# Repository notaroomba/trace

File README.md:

<h1 align="center">
  <br>
  
  <br>
  Trace
  <br>
</h1>

<h4 align="center">
A comprehensive PCB ruler with essential reference footprints, measurements, and conversions!
</h4>

<div align="center">

</div>

<p align="center">
  <a href="#key-features">Key Features</a> •
  <a href="#pcb">PCB</a> •
  <a href="#credits">Credits</a> •
  <a href="#license">License</a>
</p>

## Key Features

- **310mm x 35mm PCB ruler** with imperial and metric measurements
- **AWG gauge** for wire sizing and via hole measurements
- **Trace thickness reference** for PCB design
- **Protractor** with 5° and 10° angle markings
- **Common component footprints** including:
  - Resistors (various packages)
  - Capacitors (multiple sizes)
  - Inductors
  - Diodes and general components
  - ICs (various packages)
- **MOSFET channel type reference** silkscreen
- **Useful conversions** on the back
- **NFC Tag** to keep owner info / save more conversions/formulas/information

<video width="800" controls poster="assets/trace.jpg">
  <source src="assets/trace_nfc.mp4" type="video/mp4">
  Your browser does not support the video tag. <a href="assets/trace_nfc.mp4">Download the video</a>.
</video>

## PCB

Designed in KiCad as a practical tool for electronics engineers and hobbyists.

### Schematic

### PCB Layout

## Credits

This project uses:

- [KiCad](https://www.kicad.org/)
- [Figma](https://www.figma.com/) for protractor design
- [Hack Club Blueprint](https://blueprint.hackclub.com/)

## You may also like...

- [Cyberboard](https://github.com/NotARoomba/Cyberboard) – A Raspberry Pi Pico-sized STM32 development board with Bluetooth
- [CyberCard](https://github.com/NotARoomba/CyberCard) – A Cyberpunk themed NFC hacker card
- [Niveles De Niveles](https://github.com/NotARoomba/NivelesDeNiveles) – Real-time flood alert app
- [Linea](https://github.com/NotARoomba/Linea) – An EMR tablet
- [Tamaki](https://github.com/NotARoomba/Tamaki) – A cute HackPad

## License

MIT

---

> [notaroomba.dev](https://notaroomba.dev) &nbsp;&middot;&nbsp;
> GitHub [@NotARoomba](https://github.com/NotARoomba) &nbsp;&middot;&nbsp;

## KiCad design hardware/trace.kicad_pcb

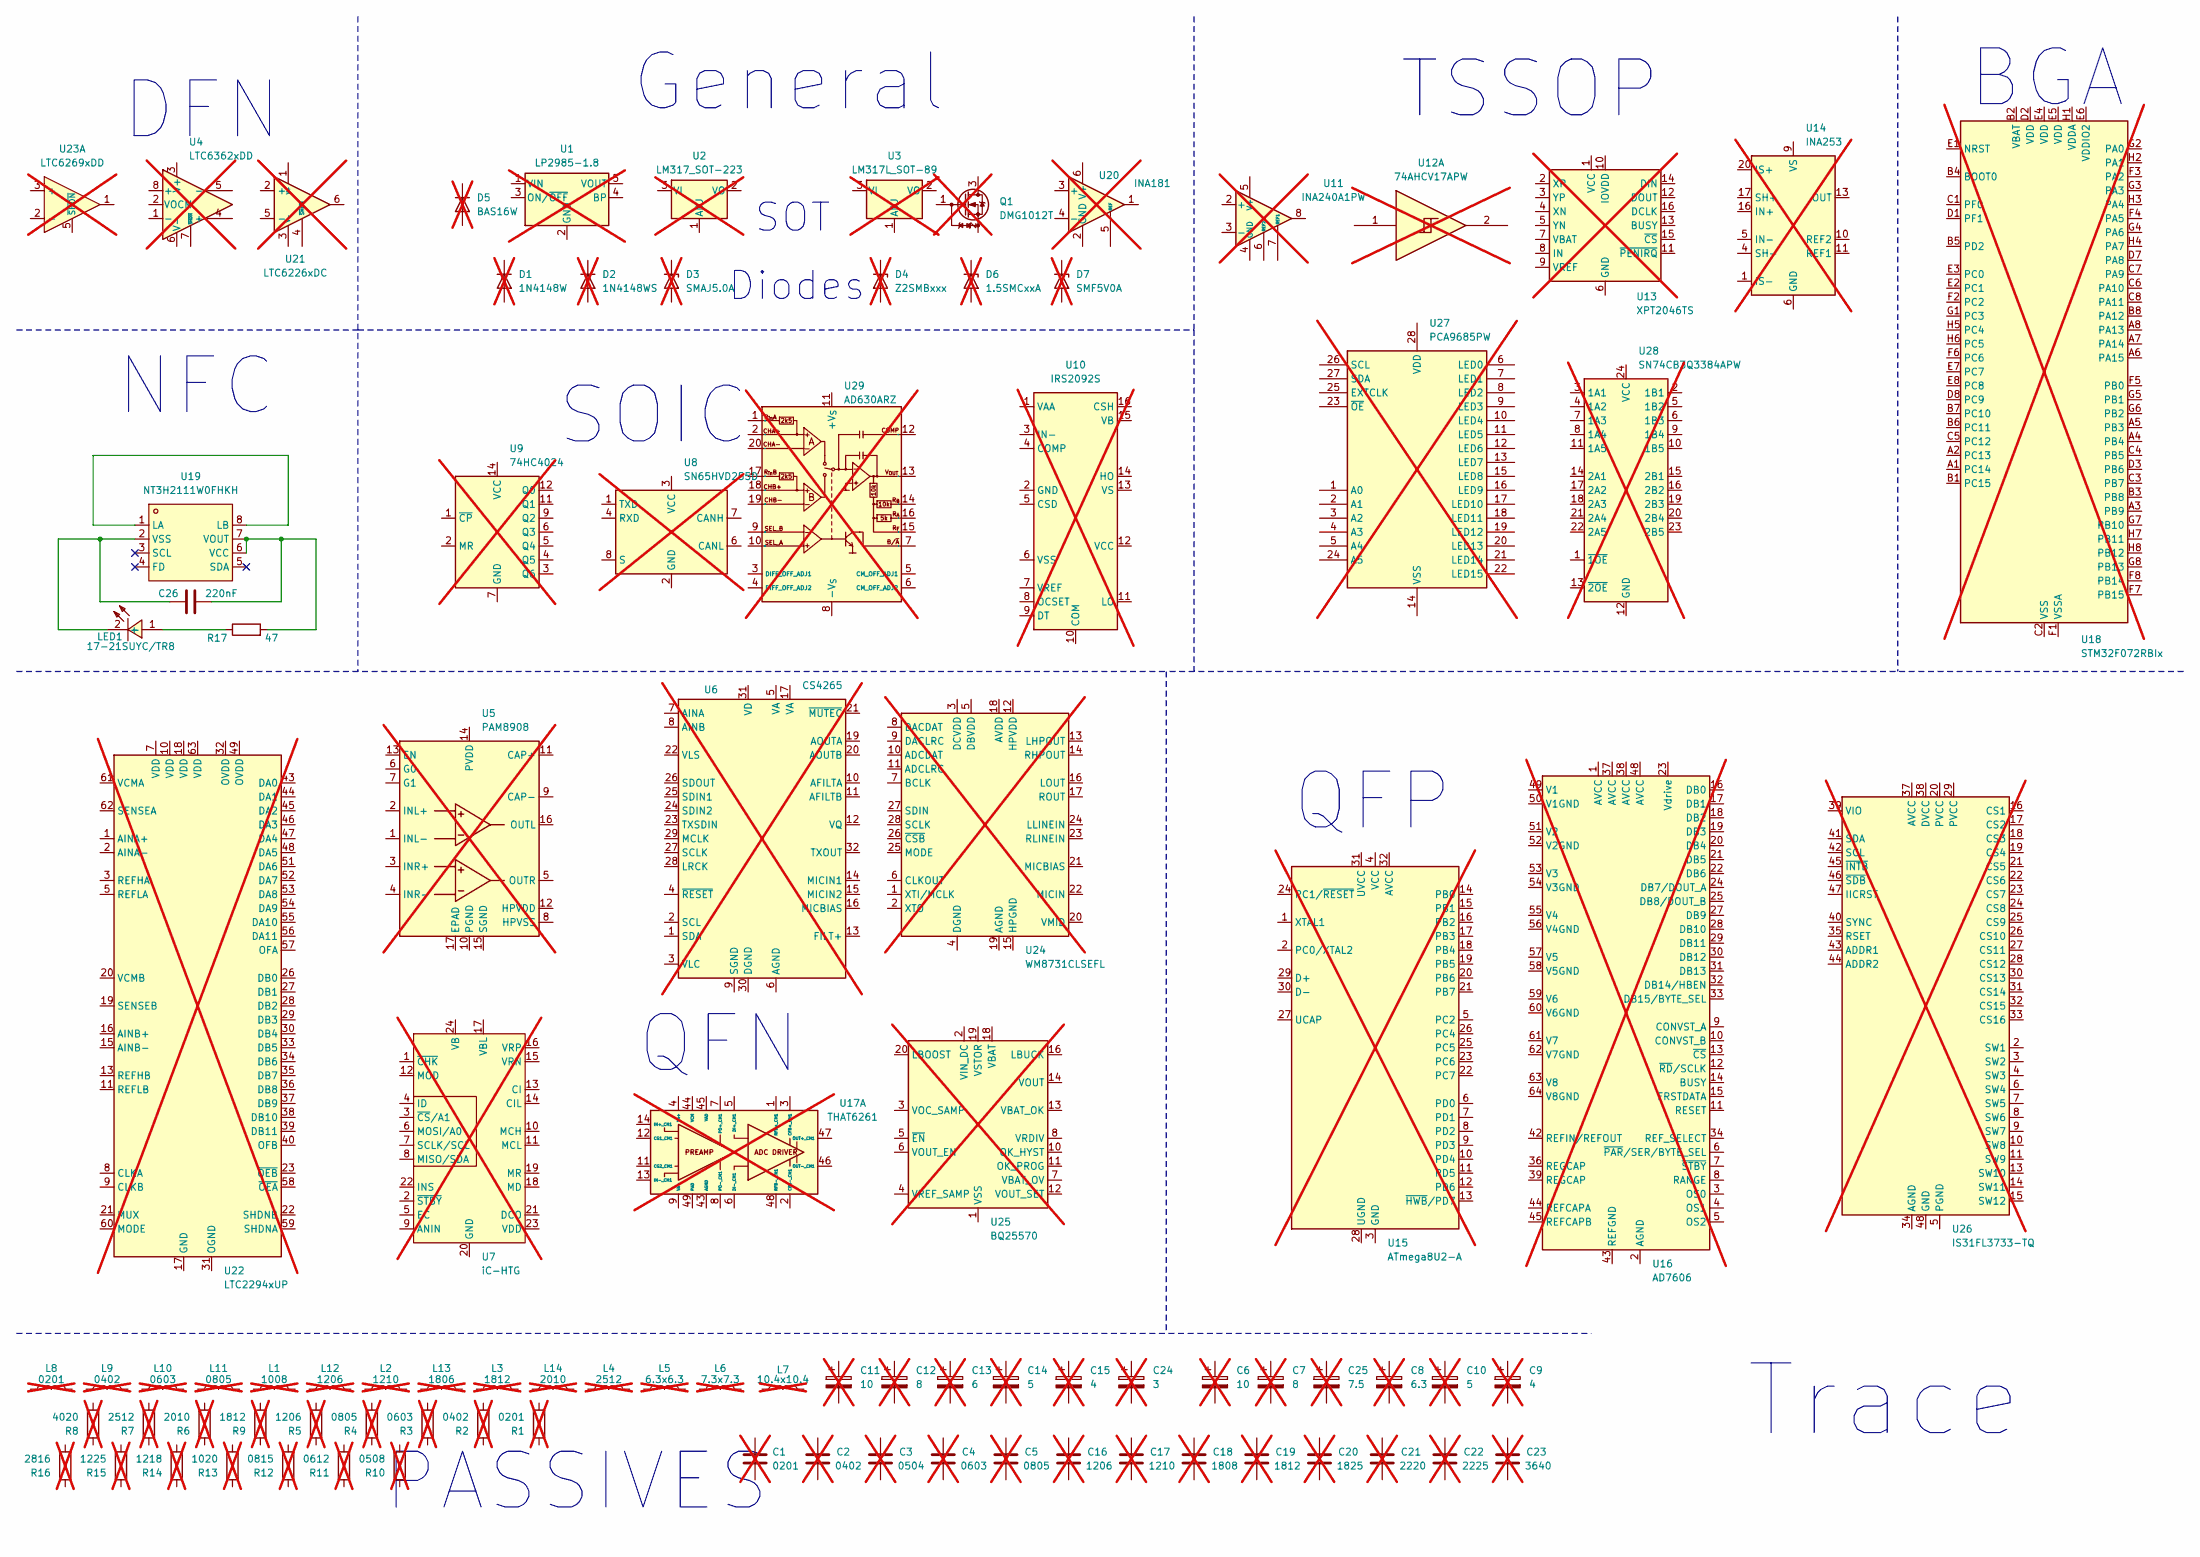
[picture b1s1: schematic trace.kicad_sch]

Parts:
C1: 0201; C_0201_0603Metric; not fitted
C2: 0402; C_0402_1005Metric; not fitted
C3: 0504; C_0504_1310Metric; not fitted
C4: 0603; C_0603_1608Metric; not fitted
C5: 0805; C_0805_2012Metric; not fitted
C6: 10; CP_Radial_D10.0mm_P5.00mm; not fitted
C7: 8; CP_Radial_D8.0mm_P3.50mm; not fitted
C8: 6.3; CP_Radial_D6.3mm_P2.50mm; not fitted
C9: 4; CP_Radial_D4.0mm_P2.00mm; not fitted
C10: 5; CP_Radial_D5.0mm_P2.00mm; not fitted
C11: 10; CP_Elec_10x10.5; not fitted
C12: 8; CP_Elec_8x10.5; not fitted
C13: 6; CP_Elec_6.3x5.9; not fitted
C14: 5; CP_Elec_5x5.7; not fitted
C15: 4; CP_Elec_4x5.3; not fitted
C16: 1206; C_1206_3216Metric; not fitted
C17: 1210; C_1210_3225Metric; not fitted
C18: 1808; C_1808_4520Metric; not fitted
C19: 1812; C_1812_4532Metric; not fitted
C20: 1825; C_1825_4564Metric; not fitted
C21: 2220; C_2220_5750Metric; not fitted
C22: 2225; C_2225_5664Metric; not fitted
C23: 3640; C_3640_9110Metric; not fitted
C24: 3; CP_Elec_3x5.4; not fitted
C25: 7.5; CP_Radial_D7.5mm_P2.50mm; not fitted
C26: 220nF; C_0603_1608Metric; LCSC C21120
D1: 1N4148W; D_SOD-123; not fitted
D2: 1N4148WS; D_SOD-323; not fitted
D3: SMAJ5.0A; D_SMA; not fitted
D4: Z2SMBxxx; D_SMB; not fitted
D5: BAS16W; SOT-323_SC-70; not fitted
D6: 1.5SMCxxA; D_SMC; not fitted
D7: SMF5V0A; D_SMF; not fitted
L1: 1008; L_1008_2520Metric; not fitted
L2: 1210; L_1210_3225Metric; not fitted
L3: 1812; L_1812_4532Metric; not fitted
L4: 2512; L_2512_6332Metric; not fitted
L5: 6.3x6.3; L_6.3x6.3_H3; not fitted
L6: 7.3x7.3; L_7.3x7.3_H4.5; not fitted
L7: 10.4x10.4; L_10.4x10.4_H4.8; not fitted
L8: 0201; L_0201_0603Metric; not fitted
L9: 0402; L_0402_1005Metric; not fitted
L10: 0603; L_0603_1608Metric; not fitted
L11: 0805; L_0805_2012Metric; not fitted
L12: 1206; L_1206_3216Metric; not fitted
L13: 1806; L_1806_4516Metric; not fitted
L14: 2010; L_2010_5025Metric; not fitted
LED1: 17-21SUYC/TR8; LED0805-R-RD; LCSC Part C2296
Q1: DMG1012T; SOT-523; not fitted
R1: 0201; R_0201_0603Metric; not fitted
R2: 0402; R_0402_1005Metric; not fitted
R3: 0603; R_0603_1608Metric; not fitted
R4: 0805; R_0805_2012Metric; not fitted
R5: 1206; R_1206_3216Metric; not fitted
R6: 2010; R_2010_5025Metric; not fitted
R7: 2512; R_2512_6332Metric; not fitted
R8: 4020; R_4020_10251Metric; not fitted
R9: 1812; R_1812_4532Metric; not fitted
R10: 0508; R_0508_1220Metric; not fitted
R11: 0612; R_0612_1632Metric; not fitted
R12: 0815; R_0815_2038Metric; not fitted
R13: 1020; R_1020_2550Metric; not fitted
R14: 1218; R_1218_3246Metric; not fitted
R15: 1225; R_1225_3264Metric; not fitted
R16: 2816; R_2816_7142Metric; not fitted
R17: 47; R_0402_1005Metric; LCSC C25118
U1: LP2985-1.8; SOT-23-5; not fitted
U2: LM317_SOT-223; SOT-223-3_TabPin2; not fitted
U3: LM317L_SOT-89; SOT-89-3; not fitted
U4: LTC6362xDD; DFN-8-1EP_3x3mm_P0.5mm_EP1.66x2.38mm; not fitted
U5: PAM8908; QFN-16-1EP_3x3mm_P0.5mm_EP1.7x1.7mm; not fitted
U6: CS4265; QFN-32-1EP_5x5mm_P0.5mm_EP3.6x3.6mm; not fitted
U7: iC-HTG; HVQFN-24-1EP_4x4mm_P0.5mm_EP2.5x2.5mm; not fitted
U8: SN65HVD255D; SOIC-8_3.9x4.9mm_P1.27mm; not fitted
U9: 74HC4024; SOIC-14_3.9x8.7mm_P1.27mm; not fitted
U10: IRS2092S; SOIC-16_3.9x9.9mm_P1.27mm; not fitted
U11: INA240A1PW; TSSOP-8_4.4x3mm_P0.65mm; not fitted
U12: 74AHCV17APW; TSSOP-14_4.4x5mm_P0.65mm; not fitted
U13: XPT2046TS; TSSOP-16_4.4x5mm_P0.65mm; not fitted
U14: INA253; TSSOP-20_4.4x6.5mm_P0.65mm; not fitted
U15: ATmega8U2-A; TQFP-32_7x7mm_P0.8mm; not fitted
U16: AD7606; LQFP-64_10x10mm_P0.5mm; not fitted
U17: THAT6261; QFN-48-1EP_7x7mm_P0.5mm_EP5.45x5.45mm; not fitted
U18: STM32F072RBIx; UFBGA-64_5x5mm_Layout8x8_P0.5mm; not fitted
U19: NT3H2111W0FHKH; XQFN-8_L1.6-W1.6-P0.50-BL_NT3H2111W0FHKH; LCSC Part C710403
U20: INA181; SOT-23-6; not fitted
U21: LTC6226xDC; DFN-6-1EP_2x2mm_P0.5mm_EP0.6x1.37mm; not fitted
U22: LTC2294xUP; QFN-64-1EP_9x9mm_P0.5mm_EP7.15x7.15mm; not fitted
U23: LTC6269xDD; DFN-10-1EP_3x3mm_P0.5mm_EP1.65x2.38mm; not fitted
U24: WM8731CLSEFL; QFN-28-1EP_5x5mm_P0.5mm_EP3.35x3.35mm; not fitted
U25: BQ25570; QFN-20-1EP_3.5x3.5mm_P0.5mm_EP2x2mm; not fitted
U26: IS31FL3733-TQ; TQFP-48-1EP_7x7mm_P0.5mm_EP5x5mm; not fitted
U27: PCA9685PW; TSSOP-28_4.4x9.7mm_P0.65mm; not fitted
U28: SN74CB3Q3384APW; TSSOP-24_4.4x7.8mm_P0.65mm; not fitted
U29: AD630ARZ; SOIC-20W_7.5x12.8mm_P1.27mm; not fitted

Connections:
unnamed: LED1.1 (+), R17.1
unnamed: C26.1, LED1.2 (-), U19.2 (VSS)
unnamed: U4.6 (V-), U4.9 (V-)
unnamed: U6.6 (AGND), U6.18 (AGND), U6.33 (AGND)
unnamed: U7.20 (GND), U7.25 (GND)
unnamed: U11.1 (GND), U11.4 (GND)
unnamed: U14.6 (GND), U14.15 (GND)
unnamed: U14.18 (IS+), U14.19 (IS+), U14.20 (IS+)
unnamed: U14.1 (IS-), U14.2 (IS-), U14.3 (IS-)
unnamed: U16.2 (AGND), U16.26 (AGND), U16.35 (AGND), U16.40 (AGND), U16.41 (AGND), U16.47 (AGND)
unnamed: U16.43 (REFGND), U16.46 (REFGND)
unnamed: U17.4 (VA+), U17.10 (VA+)
unnamed: U17.9 (VA-), U17.15 (VA-), U17.20 (VA-)
unnamed: U18.C2 (VSS), U18.D4 (VSS), U18.D5 (VSS), U18.D6 (VSS)
unnamed: U19.1 (LA), U19.8 (LB)
unnamed: C26.2, R17.2, U19.6 (VCC), U19.7 (VOUT)
unnamed: U21.3 (V-), U21.7 (V-)
unnamed: U22.17 (GND), U22.64 (GND), U22.65 (GND)
unnamed: U22.31 (OGND), U22.50 (OGND)
unnamed: U22.3 (REFHA), U22.4 (REFHA)
unnamed: U22.13 (REFHB), U22.14 (REFHB)
unnamed: U22.5 (REFLA), U22.6 (REFLA)
unnamed: U22.11 (REFLB), U22.12 (REFLB)
unnamed: U24.19 (AGND), U24.29 (AGND)
unnamed: U25.1 (VSS), U25.9 (VSS), U25.15 (VSS), U25.17 (VSS), U25.21 (VSS)
unnamed: U26.48 (GND), U26.49 (GND)
unnamed: U26.5 (PGND), U26.12 (PGND)

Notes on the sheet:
TSSOP
NFC
BGA
SOT
SOIC
DFN
PASSIVES
Trace
QFP
General
Diodes
QFN

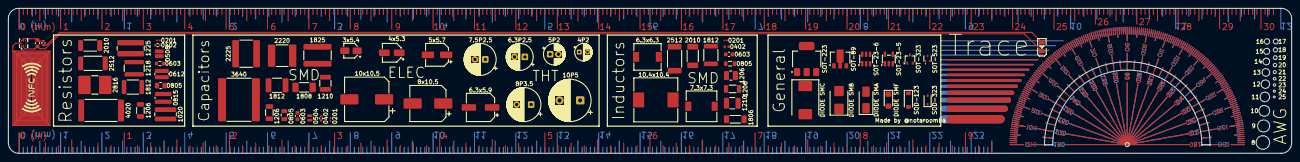
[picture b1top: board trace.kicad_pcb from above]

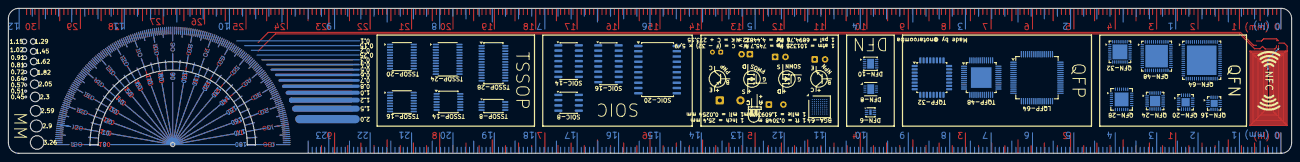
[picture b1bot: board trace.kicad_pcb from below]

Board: 2 copper layers, 309.9 x 35.0 mm, 100 parts (29 on the bottom side), 27 nets.

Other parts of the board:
E$50: NMOS-SYMB
E$51: PMOS-SYMB
E$53: LED-GUIDE
E$54: NPN-SYMB
E$59: PNP-SYMB

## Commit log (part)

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2025-11-06 added schematic
2025-11-06 added stuff
2025-11-07 finished inches
2025-11-08 stuff
2025-11-09 README and board done
2025-11-10 cost optimizing and render
2025-11-10 start of nfc antenna
2025-11-11 add nfc
2025-11-11 udpated prices
2025-11-11 udpated readme
2025-11-13 added 2nd page
2025-11-13 shipping
2025-11-13 render and banner
2025-11-18 udpated bom and stuff
2025-11-26 add in flyer
2025-11-27 update order ss
2025-12-28 ad in imges and readme
2026-05-13 fix text
